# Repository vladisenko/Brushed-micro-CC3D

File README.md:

# Brushed micro CC3D
Small size version of the CC3D flight controller. It's developed for the 90mm carbon frame (CF-01). PCB is contain receiver based on A7105, FlySky compatible. Also board have mosfet drivers for brushed motors. 

PCB with "2oz 0.8mm" option from [OSH Park](https://oshpark.com/shared_projects/dTEgwpc5).

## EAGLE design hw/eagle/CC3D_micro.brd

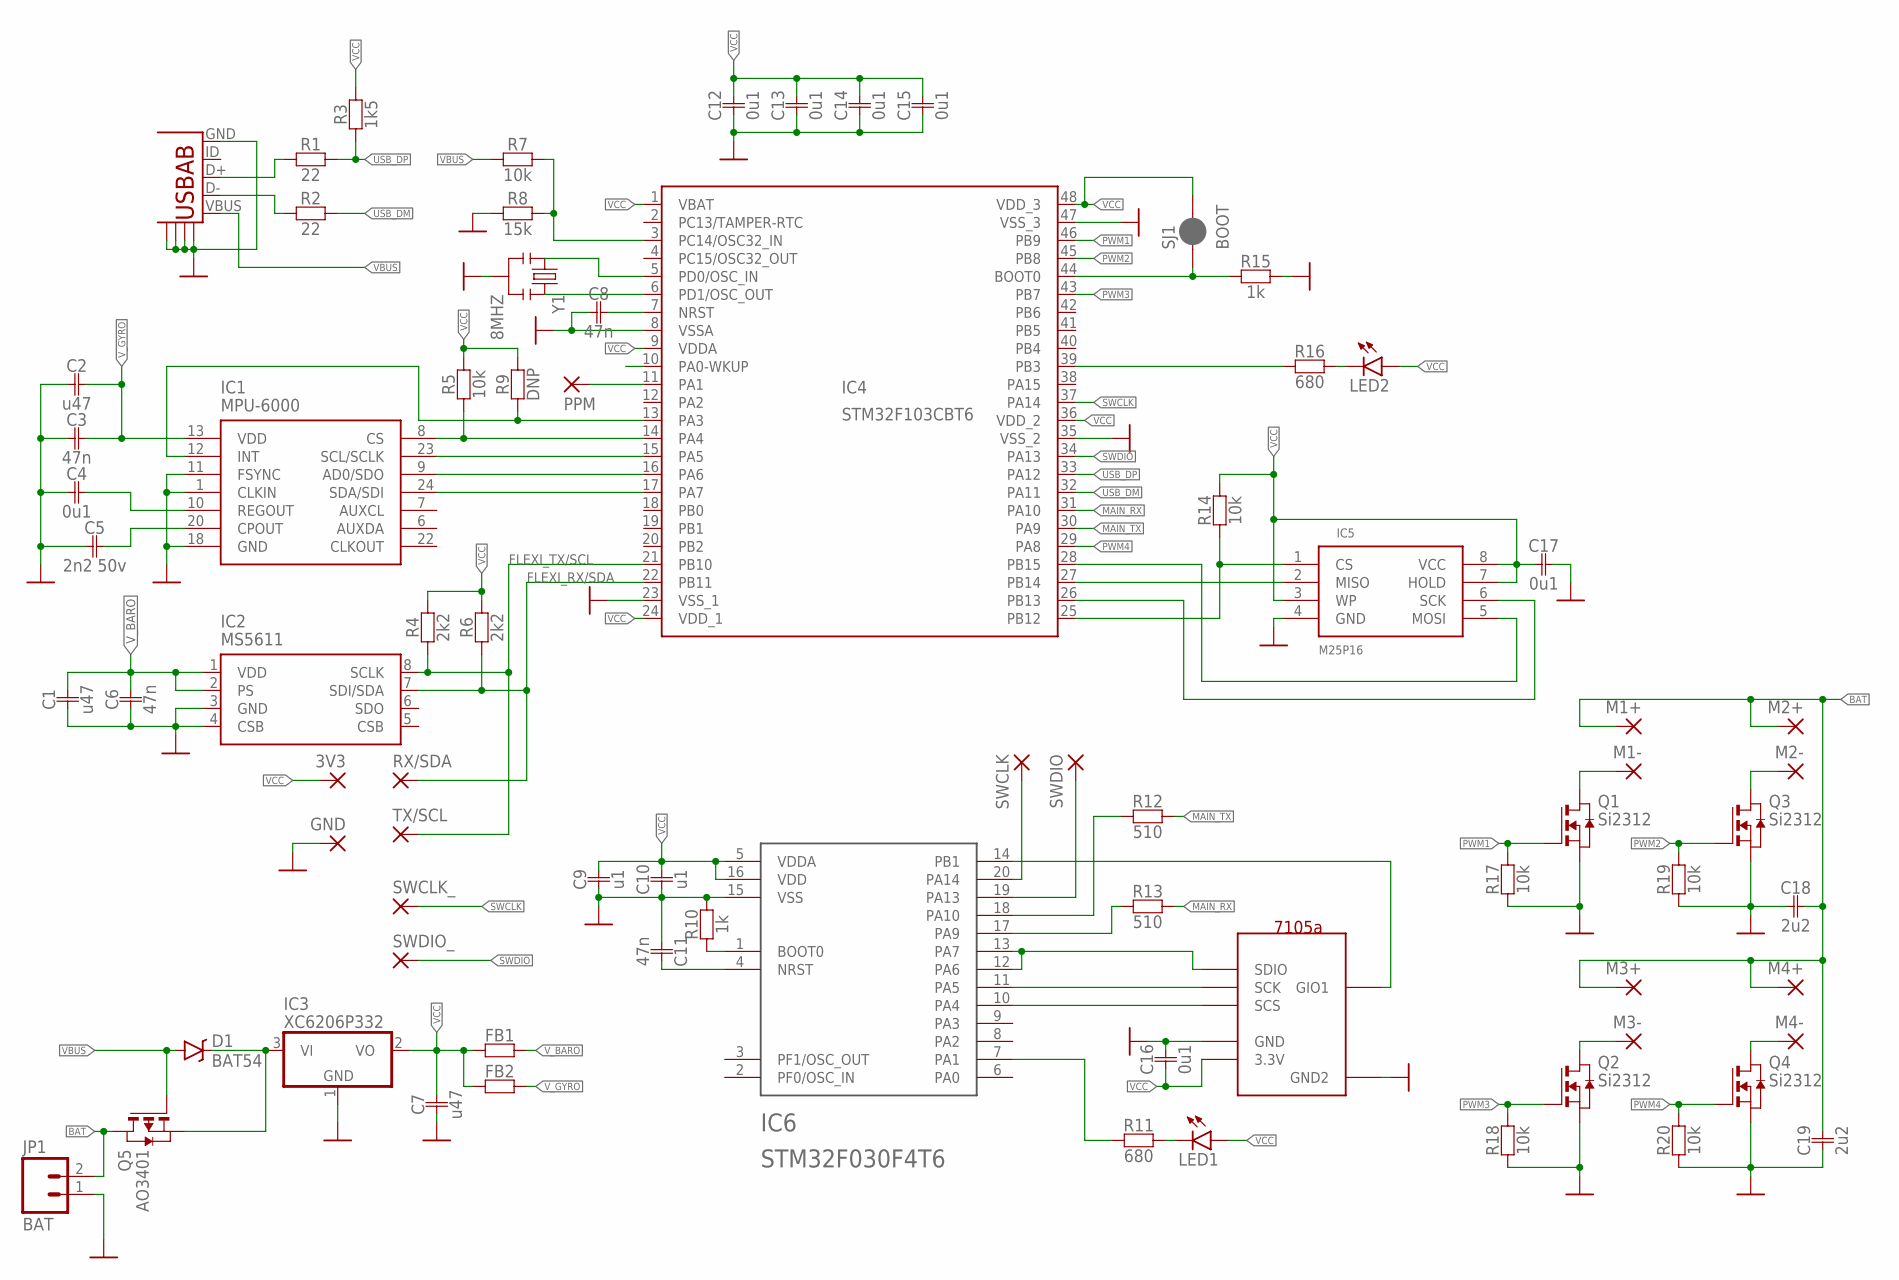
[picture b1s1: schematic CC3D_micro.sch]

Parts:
3V3: SMD2; SMD1,27-2,54
C1, C2: u47; 0402
C3, C6, C8, C11: 47n; 0402
C4, C12, C13, C14, C15, C17: 0u1; 0402
C5: 2n2 50v; 0402
C7: u47; 0805
C9, C10: u1; 0402
C16: 0u1; 0603
C18, C19: 2u2; 0805
D1: BAT54; SOD-323
FB1, FB2: R0603; 0603
GND: SMD2; SMD1,27-2,54
IC1: MPU-6000; QFN-24-TESTING
IC2: MS5611; LGA8
IC3: XC6206P332; SOT23
IC4: STM32F103CBT6; LQFP48
IC5: M25P16; SO08
IC6: STM32F030F4T6; TSSOP-20
JP1: BAT; 1X02_NO_SILK
LED1, LED2: LED0603; LED-0603
M1+, M1-, M2+, M2-, M3+, M3-, M4+, M4-: SMD2; SMD1,27-2,54
PPM: SMD2; SMD1,27-2,54
Q1, Q2, Q3, Q4: Si2312; SOT-23
Q5: AO3401; SOT-23
R1, R2: 22; 0402
R3: 1k5; 0402
R4, R6: 2k2; 0402
R5, R7, R14, R17, R18, R19, R20: 10k; 0402
R8: 15k; 0402
R9: DNP; 0402
R10, R15: 1k; 0402
R11, R16: 680; 0402
R12, R13: 510; 0402
RX/SDA: SMD2; SMD1,27-2,54
SJ1: BOOT; PAD-JUMPER-2-NC_BY_PASTE_YES_SILK
SWCLK: SMD2; SMD1,27-2,54
SWCLK_: SMD2; SMD1,27-2,54
SWDIO: SMD2; SMD1,27-2,54
SWDIO_: SMD2; SMD1,27-2,54
TX/SCL: SMD2; SMD1,27-2,54
U$1: microUSB; UNTITLED_USB-AB-MICRO-SMD
U$2: XL7105-SL-B-TH; XL7105-SY-B
Y1: 8MHZ; RESONATOR-SMD

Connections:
BAT: C18.P$2, C19.P$2, JP1.2, M1+.1, M2+.1, M3+.1, M4+.1, Q5.1 (D)
FLEXI_RX/SDA: IC2.7 (SDI/SDA), IC4.22 (PB11), R6.P$1, RX/SDA.1
FLEXI_TX/SCL: IC2.8 (SCLK), IC4.21 (PB10), R4.P$1, TX/SCL.1
GND: C1.P$1, C2.P$1, C3.P$1, C4.P$1, C5.P$1, C6.P$1, C7.P$1, C8.P$1, C9.P$1, C10.P$2, C11.P$1, C12.P$1, C13.P$1, C14.P$1, C15.P$1, C16.P$2, C17.P$2, C18.P$1, C19.P$1, GND.1, IC1.1 (CLKIN), IC1.11 (FSYNC), IC1.18 (GND), IC2.3 (GND), IC2.4 (CSB), IC3.1 (GND), IC4.8 (VSSA), IC4.23 (VSS_1), IC4.35 (VSS_2), IC4.47 (VSS_3), IC5.4 (GND), IC6.15 (VSS), JP1.1, Q1.2 (S), Q2.2 (S), Q3.2 (S), Q4.2 (S), R8.P$2, R10.P$2, R15.P$2, R17.P$1, R18.P$1, R19.P$1, R20.P$1, U$1.GND, U$1.GND@1, U$1.GND@2, U$1.GND@3, U$1.GND@4, U$2.P$2 (GND), U$2.P$6 (GND2), Y1.2
M1+: M1-.1, Q1.1 (D)
M2+: M2-.1, Q3.1 (D)
M3+: M3-.1, Q2.1 (D)
M4+: M4-.1, Q4.1 (D)
MAIN_RX: IC4.31 (PA10), R13.P$2
MAIN_TX: IC4.30 (PA9), R12.P$2
unnamed: IC1.12 (INT), IC4.13 (PA3), R9.P$1
unnamed: IC1.8 (CS), IC4.14 (PA4), R5.P$1
unnamed: IC1.23 (SCL/SCLK), IC4.15 (PA5)
unnamed: IC1.9 (AD0/SDO), IC4.16 (PA6)
unnamed: IC1.24 (SDA/SDI), IC4.17 (PA7)
unnamed: IC6.1 (BOOT0), R10.P$1
unnamed: IC4.25 (PB12), IC5.1 (CS), R14.P$1
unnamed: IC4.26 (PB13), IC5.6 (SCK)
unnamed: IC4.27 (PB14), IC5.2 (MISO)
unnamed: IC4.28 (PB15), IC5.5 (MOSI)
unnamed: IC4.6 (PD1/OSC_OUT), Y1.3
unnamed: IC6.14 (PB1), U$2.P$7 (GIO1)
unnamed: IC4.39 (PB3), R16.P$1
unnamed: LED2.C, R16.P$2
unnamed: IC4.3 (PC14/OSC32_IN), R7.P$2, R8.P$1
unnamed: R2.P$2, U$1.D-
unnamed: IC4.44 (BOOT0), R15.P$1, SJ1.1
unnamed: R1.P$2, U$1.D+
unnamed: IC6.10 (PA4), U$2.P$3 (SCS)
unnamed: IC6.11 (PA5), U$2.P$4 (SCK)
unnamed: LED1.C, R11.P$2
unnamed: IC6.12 (PA6), IC6.13 (PA7), U$2.P$5 (SDIO)
unnamed: IC6.17 (PA9), R13.P$1
unnamed: IC6.18 (PA10), R12.P$1
unnamed: IC6.19 (PA13), SWDIO.1
unnamed: IC6.20 (PA14), SWCLK.1
unnamed: IC6.7 (PA1), R11.P$1
unnamed: C4.P$2, IC1.10 (REGOUT)
unnamed: IC4.5 (PD0/OSC_IN), Y1.1
unnamed: C5.P$2, IC1.20 (CPOUT)
unnamed: IC4.11 (PA1), PPM.1
unnamed: D1.C, IC3.3 (VI), Q5.2 (S)
unnamed: C8.P$2, IC4.7 (NRST)
unnamed: C11.P$2, IC6.4 (NRST)
PWM1: IC4.46 (PB9), Q1.3 (G), R17.P$2
PWM2: IC4.45 (PB8), Q3.3 (G), R19.P$2
PWM3: IC4.43 (PB7), Q2.3 (G), R18.P$2
PWM4: IC4.29 (PA8), Q4.3 (G), R20.P$2
SWCLK: IC4.37 (PA14), SWCLK_.1
SWDIO: IC4.34 (PA13), SWDIO_.1
USB_DM: IC4.32 (PA11), R2.P$1
USB_DP: IC4.33 (PA12), R1.P$1, R3.P$2
VBUS: D1.A, Q5.3 (G), R7.P$1, U$1.VBUS
VCC: 3V3.1, C7.P$2, C9.P$2, C10.P$1, C12.P$2, C13.P$2, C14.P$2, C15.P$2, C16.P$1, C17.P$1, FB1.P$1, FB2.P$1, IC3.2 (VO), IC4.1 (VBAT), IC4.9 (VDDA), IC4.24 (VDD_1), IC4.36 (VDD_2), IC4.48 (VDD_3), IC5.3 (WP), IC5.7 (HOLD), IC5.8 (VCC), IC6.5 (VDDA), IC6.16 (VDD), LED1.A, LED2.A, R3.P$1, R4.P$2, R5.P$2, R6.P$2, R9.P$2, R14.P$2, SJ1.2, U$2.P$1 (3.3V)
V_BARO: C1.P$2, C6.P$2, FB1.P$2, IC2.1 (VDD), IC2.2 (PS)
V_GYRO: C2.P$2, C3.P$2, FB2.P$2, IC1.13 (VDD)

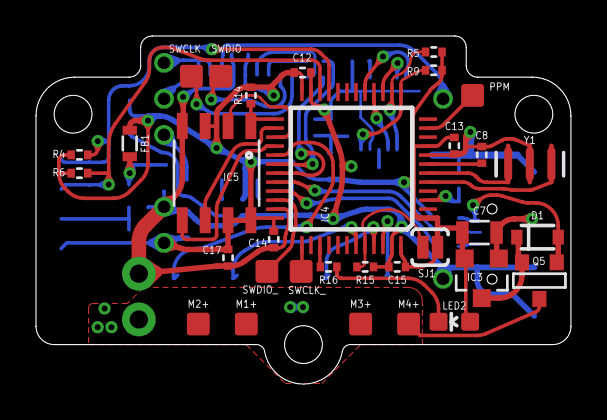
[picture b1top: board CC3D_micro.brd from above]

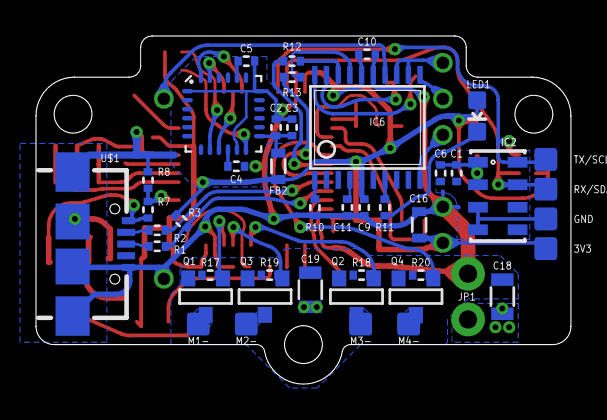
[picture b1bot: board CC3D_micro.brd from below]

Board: 2 copper layers, 29.7 x 19.3 mm, 77 parts (45 on the bottom side), 56 nets.

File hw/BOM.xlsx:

Part | Value | Package
C1 | u47 | 0402
C2 | u47 | 0402
C3 | 47n | 0402
C4 | 0u1 | 0402
C5 | 2n2 50v | 0402
C6 | 47n | 0402
C7 | u47 | 0805
C8 | 47n | 0402
C9 | u1 | 0402
C10 | u1 | 0402
C11 | 47n | 0402
C12 | 0u1 | 0402
C13 | 0u1 | 0402
C14 | 0u1 | 0402
C15 | 0u1 | 0402
C16 | 0u1 | 0603
C17 | 0u1 | 0402
C18 | 2u2 | 0805
C19 | 2u2 | 0805
D1 | BAT54 | SOD-323
FB1 |  | 0603
FB2 |  | 0603
IC1 | MPU-6000 | QFN-24
IC2 | MS5611 | LGA8
IC3 | XC6206P332 | SOT23
IC4 | STM32F103CBT6 | LQFP48
IC5 | M25P16 | SO08
IC6 | STM32F030F4T6 | TSSOP-20
JP1 | BAT | 1X02
LED1 |  | LED-0603
LED2 |  | LED-0603
Q1 | Si2312 | SOT-23
Q2 | Si2312 | SOT-23
Q3 | Si2312 | SOT-23
Q4 | Si2312 | SOT-23
Q5 | AO3401 | SOT-23
R1 | 22R | 0402
R2 | 22R | 0402
R3 | 1k5 | 0402
R4 | 2k2 | 0402
R5 | 10k | 0402
R6 | 2k2 | 0402
R7 | 10k | 0402
R8 | 15k | 0402
R9 | DNP | 0402
R10 | 1k | 0402
R11 | 680R | 0402
R12 | 510R | 0402
R13 | 510R | 0402
R14 | 10k | 0402
R15 | 1k | 0402
R16 | 680R | 0402
R17 | 10k | 0402
R18 | 10k | 0402
R19 | 10k | 0402
R20 | 10k | 0402
U$1 | microUSB
U$2 |  | XL7105-SY-B
Y1 | CSTCE8.000M

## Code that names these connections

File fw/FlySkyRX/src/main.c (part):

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FlySky compatible receiver with DSM-like output. Tested with LibrePilot CC3D,
Cleanflight and Betaflight.
After the first turn on the receiver automatically switches to bind mode.
For manual binding pin PA13 and PA14 must be closed before power up. 

Sources:
	http://www.rcgroups.com/forums/showthread.php?t=1921870
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	
	RCC->AHBENR |= RCC_AHBENR_GPIOAEN;
	
	GPIOA->MODER =	(1U << 1*2) |			// PA1 - LED - GPout,
					(1U << 4*2) |			// PA4 - CS A7105 - GPout,
					(2U << 5*2) |			// PA5 - SCK A7105 - AF,
					(2U << 6*2) |			// PA6 - DIO A7105 - AF,
					(2U << 7*2) |			// PA7 - DIO A7105 - AF,
					(2U << 13*2) |			// PA13 - SDWIO - AF,
					(2U << 14*2) ;			// PA14 - SWCLK - AF.
	
	GPIOA->OTYPER = (1 << 1);				// PA1 - LED - open drain
	
	GPIOA->PUPDR =	(2U << 0*2) |			// PA0 - Pull-down,
					(2U << 2*2) |			// PA2 - Pull-down,
					(2U << 3*2) |			// PA3 - Pull-down,
					(2U << 6*2) |			// PA6 - Pull-down,
					(2U << 8*2) |			// PA8 - Pull-down,
					(2U << 10*2) |			// PA10 - Pull-down,
					(2U << 11*2) |			// PA11 - Pull-down,
					(2U << 12*2) |			// PA12 - Pull-down,
					(2U << 15*2);			// PA15 - Pull-down.
					
	GPIOA->OSPEEDR =(3U << 5*2) |			// PA5 - SCK A7105 - high speed,
					(3U << 7*2) |			// PA7 - DIO A7105 - high speed,
					(3U << 13*2);			// PA13 - SDWIO - high speed.
	

	GPIOA->BSRR = GPIO_BSRR_BS_4 | GPIO_BSRR_BR_7 | GPIO_BSRR_BR_5;
	
	
	RCC->AHBENR |= RCC_AHBENR_GPIOBEN;
	GPIOB->PUPDR =	(1U << 1*2);			// PB1 - Pull-up.

	
	RCC->APB2ENR |= RCC_APB2ENR_SPI1EN;
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	
	RCC->AHBENR |= RCC_AHBENR_GPIOAEN;
	
	GPIOA->MODER = 0x10000000 | (GPIOA->MODER & ~0x3C000000);	// PA13 - GP in,
																// PA14 - GP out.
	if ((GPIOA->IDR & (1<<13)) == 0) res = 1;
	
	GPIOA->MODER = 0x28000000 | (GPIOA->MODER & ~0x3C000000);	// PA13 - SDWIO - AF,
																// PA14 - SWCLK - AF.
	return res;
}

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
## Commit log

2016-08-26 :tada: Added .gitattributes
2016-08-26 add hw
2016-09-11 hw v0.2
2016-09-11 update schematic
2016-09-11 add receiver fw
2016-09-11 fix misprint
2016-09-17 add BOM
2016-10-05 change DSM header
2016-10-05 add photo
2016-10-05 add small size photo
2016-10-22 Revert "Update README.md"
    This reverts commit 8bbd6640aacf3b1fad85646f990d86335a368545.
2016-10-22 Revert "Revert "Update README.md""
    This reverts commit 6f11226e005ede1fca4f9e85242f1223754367f8.

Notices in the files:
parts and their libraries:
SparkFun-LED: Licensing: Creative Commons ShareAlike 4.0 International - https://creativecommons.org/licenses/by-sa/4.0
